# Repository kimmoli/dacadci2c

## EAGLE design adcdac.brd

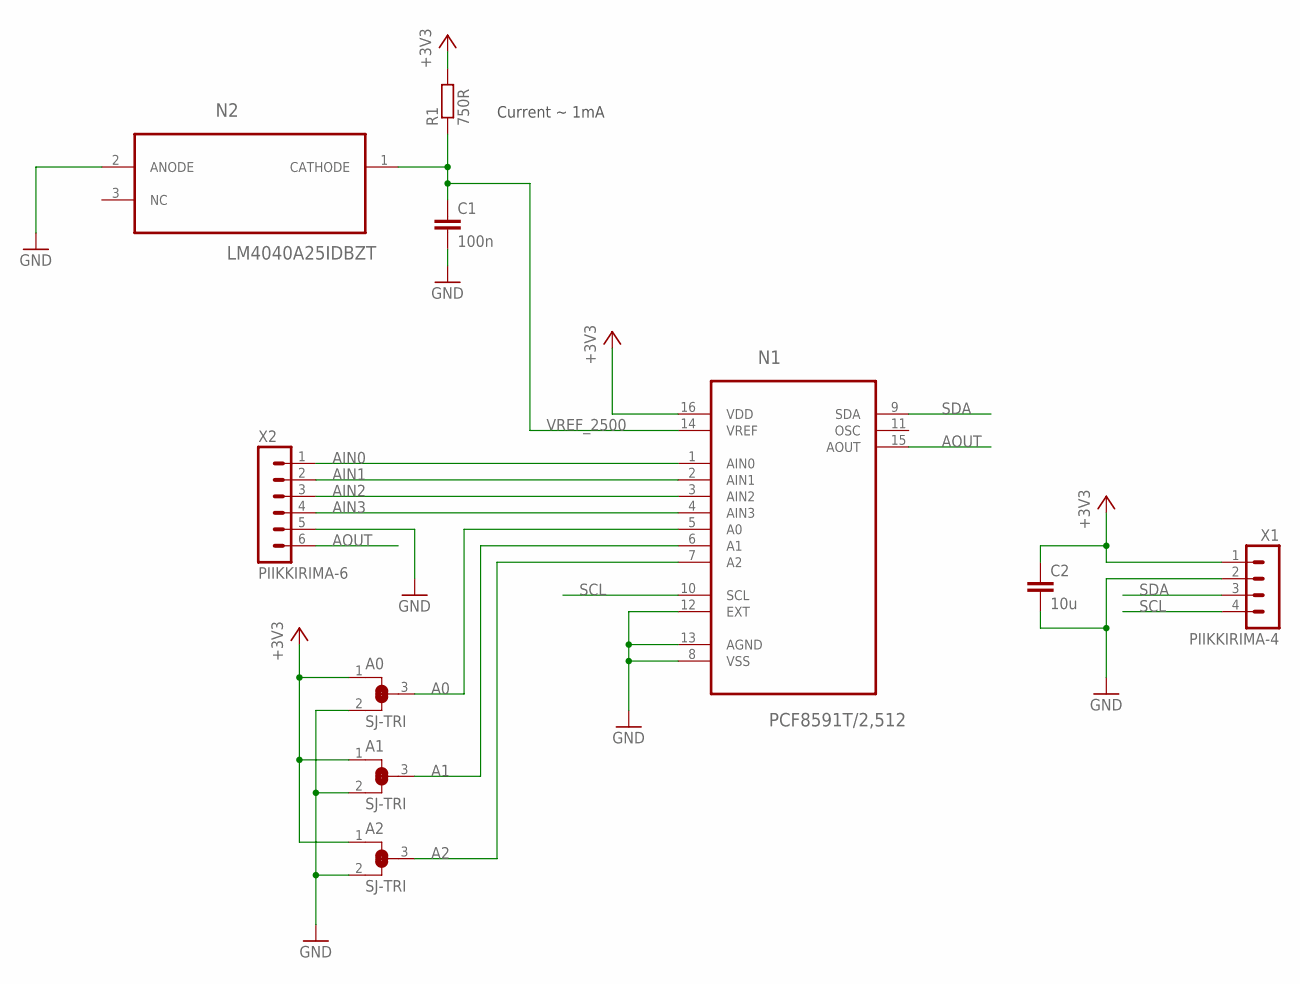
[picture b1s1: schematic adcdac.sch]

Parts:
A0, A1, A2: SJ-TRI; SJ-SMALL-TRI
C1: 100n; C0603
C2: 10u; C0805
N1: PCF8591T/2,512; SOIC127P1032X265-16N
N2: LM4040A25IDBZT; SOT95P237X112-3N
R1: 750R; R0603
X1: PIIKKIRIMA-4
X2: PIIKKIRIMA-6

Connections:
+3V3: A0.1, A1.1, A2.1, C2.1, N1.16 (VDD), R1.2, X1.1
A0: A0.3, N1.5 (A0)
A1: A1.3, N1.6 (A1)
A2: A2.3, N1.7 (A2)
AIN0: N1.1 (AIN0), X2.1
AIN1: N1.2 (AIN1), X2.2
AIN2: N1.3 (AIN2), X2.3
AIN3: N1.4 (AIN3), X2.4
AOUT: N1.15 (AOUT), X2.6
GND: A0.2, A1.2, A2.2, C1.2, C2.2, N1.8 (VSS), N1.12 (EXT), N1.13 (AGND), N2.2 (ANODE), X1.2, X2.5
SCL: N1.10 (SCL), X1.4
SDA: N1.9 (SDA), X1.3
VREF_2500: C1.1, N1.14 (VREF), N2.1 (CATHODE), R1.1

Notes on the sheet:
Current ~ 1mA

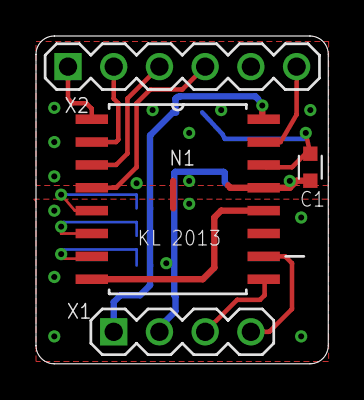
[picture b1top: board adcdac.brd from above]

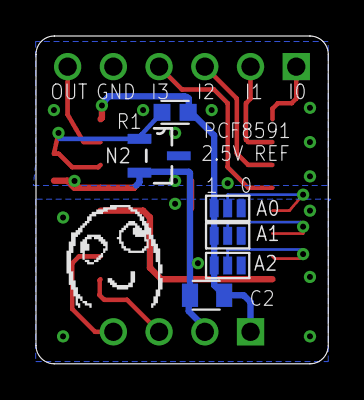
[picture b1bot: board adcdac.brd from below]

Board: 2 copper layers, 16.2 x 18.2 mm, 11 parts (7 on the bottom side), 13 nets.

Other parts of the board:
U$1: DAFUG
